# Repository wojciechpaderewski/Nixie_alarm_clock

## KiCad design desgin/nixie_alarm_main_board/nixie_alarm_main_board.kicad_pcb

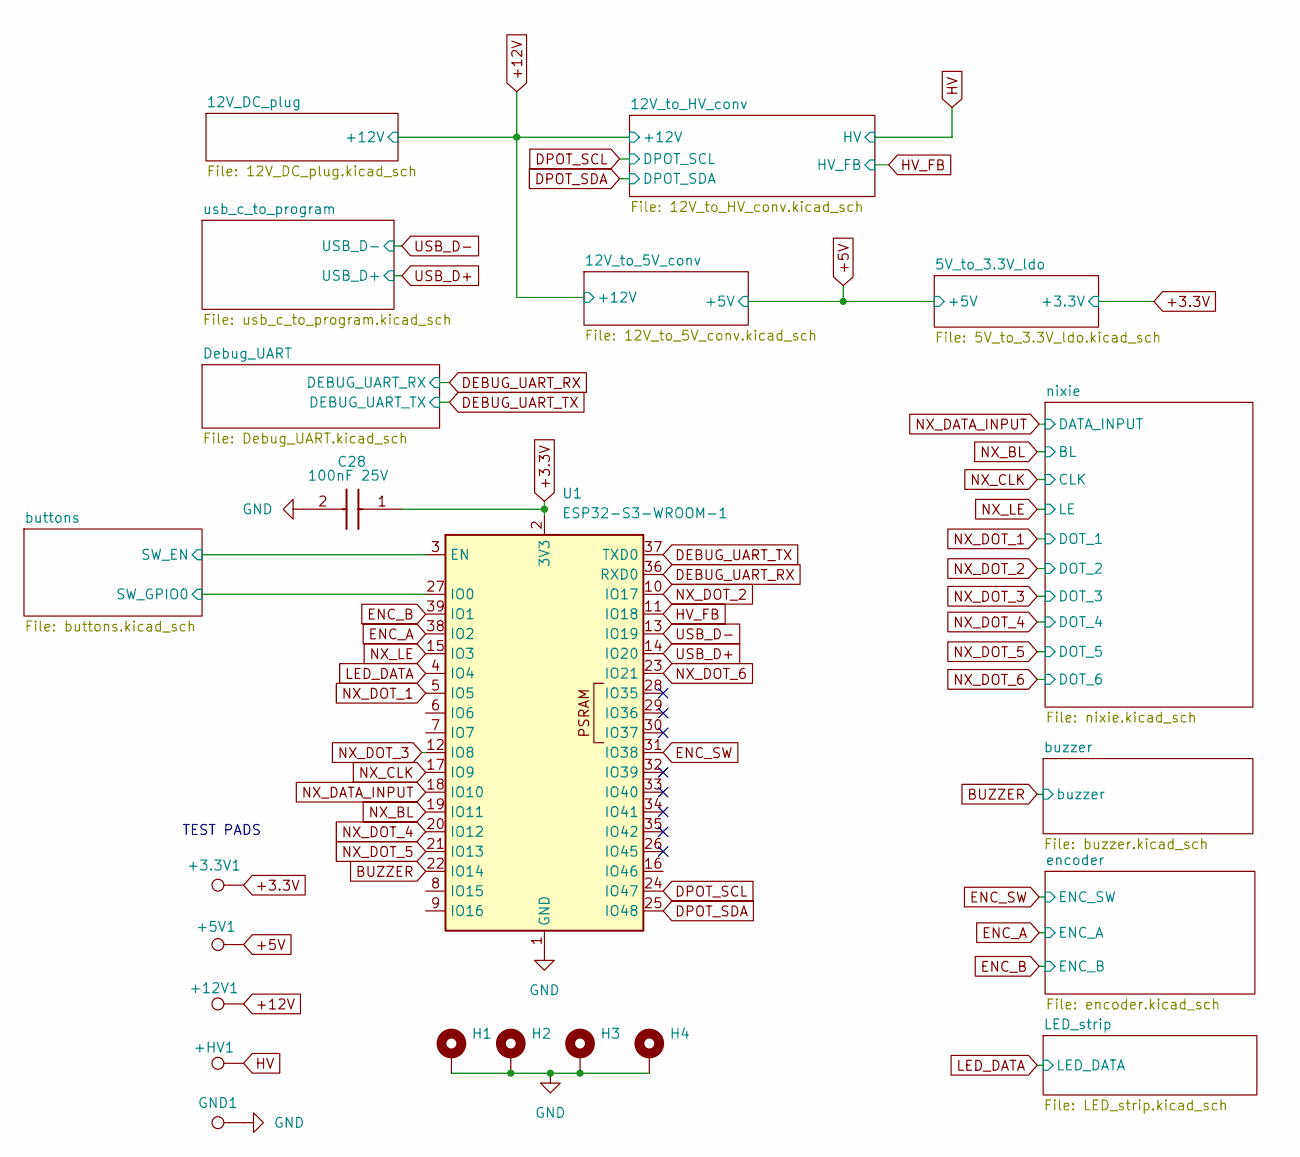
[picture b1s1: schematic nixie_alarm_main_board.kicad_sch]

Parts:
+3.3V1: +3.3V; TestPoint_Pad_D2.0mm
+5V1: +5V; TestPoint_Pad_D2.0mm
+12V1: +12V; TestPoint_Pad_D2.0mm
+HV1: +HV; TestPoint_Pad_D2.0mm
C28: 100nF 25V; C_0805_2012Metric_Pad1.18x1.45mm_HandSolder; Mouser Part Number 81-GRM033R71E101KA1J
GND1: GND; TestPoint_Pad_D2.0mm
H1, H2, H3, H4: MountingHole_Pad; MountingHole_3.2mm_M3_Pad_Via
U1: ESP32-S3-WROOM-1

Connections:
+3.3V: +3.3V1.1, C28.1, U1.2 (3V3); also elsewhere on the board
+5V: +5V1.1; also elsewhere on the board
+12V: +12V1.1; also elsewhere on the board
/buttons/SW_EN: U1.3 (EN); also elsewhere on the board
/buttons/SW_GPIO0: U1.27 (IO0); also elsewhere on the board
BUZZER: U1.22 (IO14); also elsewhere on the board
DEBUG_UART_RX: U1.36 (RXD0); also elsewhere on the board
DEBUG_UART_TX: U1.37 (TXD0); also elsewhere on the board
DPOT_SCL: U1.24 (IO47); also elsewhere on the board
DPOT_SDA: U1.25 (IO48); also elsewhere on the board
ENC_A: U1.38 (IO2); also elsewhere on the board
ENC_B: U1.39 (IO1); also elsewhere on the board
ENC_SW: U1.31 (IO38); also elsewhere on the board
GND: C28.2, GND1.1, H1.1, H2.1, H3.1, H4.1, U1.1 (GND), U1.40 (GND), U1.41 (GND); also elsewhere on the board
HV: +HV1.1; also elsewhere on the board
HV_FB: U1.11 (IO18); also elsewhere on the board
LED_DATA: U1.4 (IO4); also elsewhere on the board
NX_BL: U1.19 (IO11); also elsewhere on the board
NX_CLK: U1.17 (IO9); also elsewhere on the board
NX_DATA_INPUT: U1.18 (IO10); also elsewhere on the board
NX_DOT_1: U1.5 (IO5); also elsewhere on the board
NX_DOT_2: U1.10 (IO17); also elsewhere on the board
NX_DOT_3: U1.12 (IO8); also elsewhere on the board
NX_DOT_4: U1.20 (IO12); also elsewhere on the board
NX_DOT_5: U1.21 (IO13); also elsewhere on the board
NX_DOT_6: U1.23 (IO21); also elsewhere on the board
NX_LE: U1.15 (IO3); also elsewhere on the board
USB_D+: U1.14 (IO20); also elsewhere on the board
USB_D-: U1.13 (IO19); also elsewhere on the board

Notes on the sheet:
TEST PADS

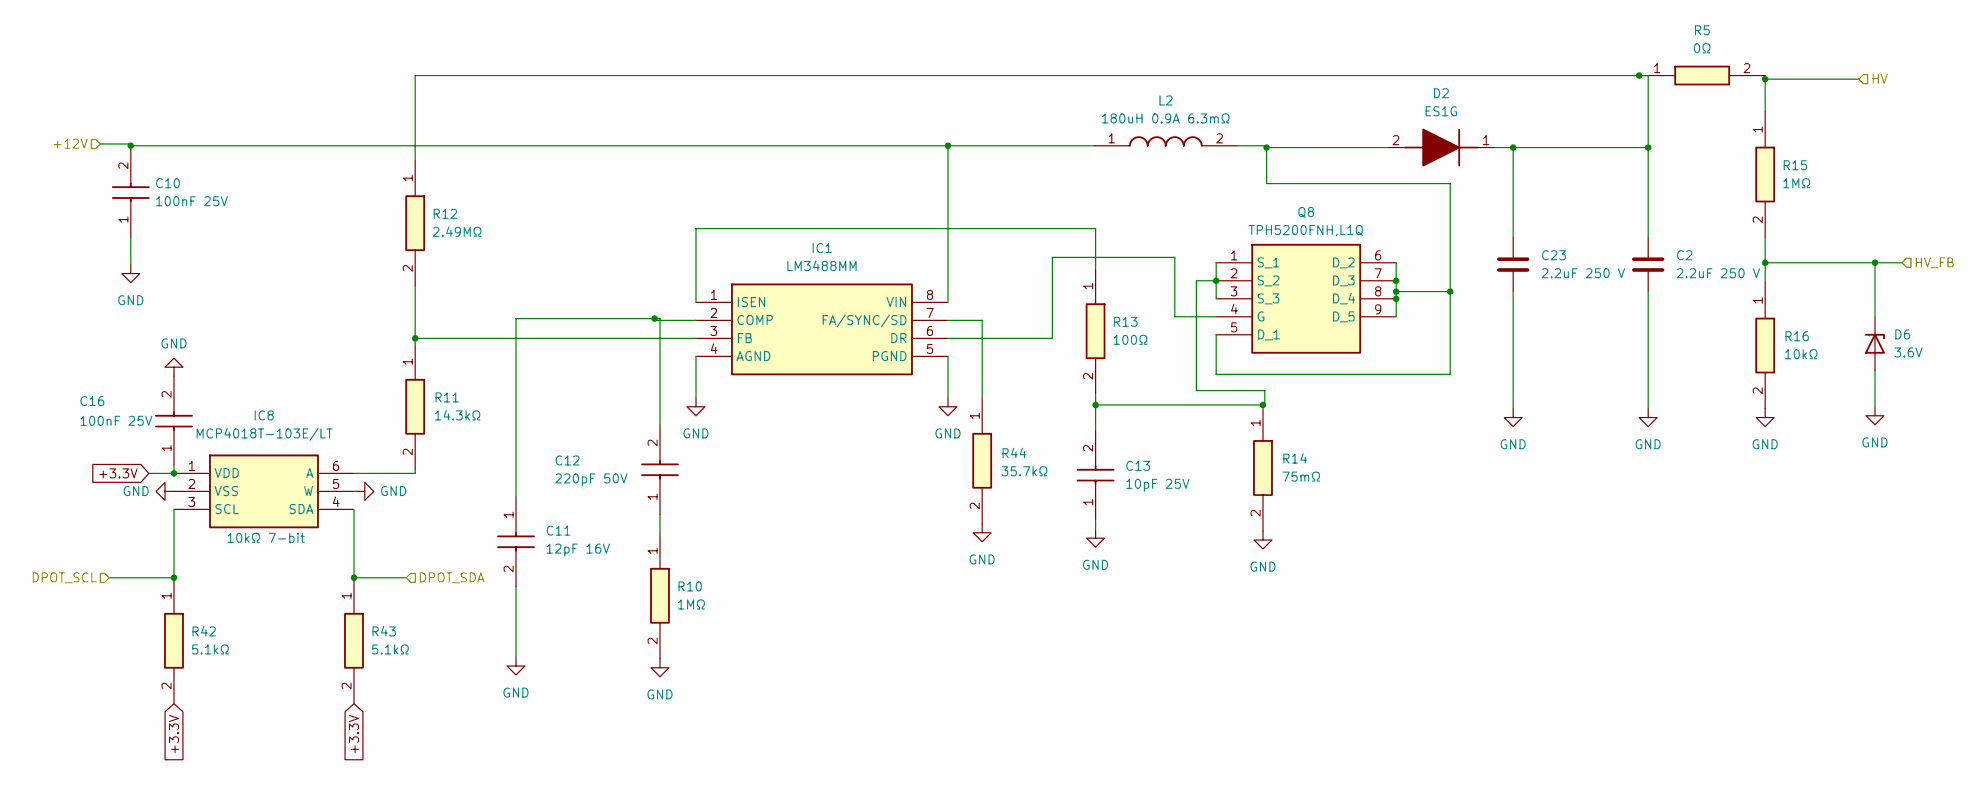
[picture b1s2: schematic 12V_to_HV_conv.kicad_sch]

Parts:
C2, C23: 2.2uF 250 V; C_2220_5750Metric_Pad1.97x5.40mm_HandSolder
C10, C16: 100nF 25V; C_0805_2012Metric_Pad1.18x1.45mm_HandSolder; Mouser Part Number 81-GRM033R71E101KA1J
C11: 12pF 16V; C0805; Mouser Part Number 80-C0805C332K5R
C12: 220pF 50V; C_0805_2012Metric_Pad1.18x1.45mm_HandSolder; Mouser Part Number 81-GRM033R71E101KA1J
C13: 10pF 25V; C_0805_2012Metric_Pad1.18x1.45mm_HandSolder; Mouser Part Number 81-GRM033R71E101KA1J
D2: ES1G; DIOM5227X260N; Mouser Part Number 512-ES1G
D6: 3.6V; D_0805_2012Metric_Pad1.15x1.40mm_HandSolder
IC1: LM3488MM; SOP65P490X110-8N; Mouser Part Number 926-LM3488MM
IC8: MCP4018T-103E/LT; SOT65P210X110-6N; Mouser Part Number 579-MCP4018T502ELT
L2: 180uH 0.9A 6.3mΩ; L_12x12mm_H6mm; Mouser Part Number 710-74437529203331
Q8: TPH5200FNH,L1Q; TPHR6503PL1LQ; Mouser Part Number 757-TPHR6503PL1LQ
R5: 0Ω; R_0805_2012Metric_Pad1.20x1.40mm_HandSolder; Mouser Part Number 71-CRCW0402-2.74K-E3
R10, R15: 1MΩ; R_1206_3216Metric_Pad1.30x1.75mm_HandSolder; Mouser Part Number 71-CRCW0402-2.74K-E3
R11: 14.3kΩ; R_0805_2012Metric_Pad1.20x1.40mm_HandSolder; Mouser Part Number 71-CRCW0402-2.74K-E3
R12: 2.49MΩ; R_1206_3216Metric_Pad1.30x1.75mm_HandSolder; Mouser Part Number 71-CRCW0402-2.74K-E3
R13: 100Ω; R_0805_2012Metric_Pad1.20x1.40mm_HandSolder; Mouser Part Number 71-CRCW0402-2.74K-E3
R14: 75mΩ; R_0805_2012Metric_Pad1.20x1.40mm_HandSolder; Mouser Part Number 667-ERJ-UP6D5101V
R16: 10kΩ; R_0805_2012Metric_Pad1.20x1.40mm_HandSolder; Mouser Part Number 71-CRCW0402-2.74K-E3
R42, R43: 5.1kΩ; R_0805_2012Metric_Pad1.20x1.40mm_HandSolder; Mouser Part Number 667-ERJ-UP6D5101V
R44: 35.7kΩ; R_0805_2012Metric_Pad1.20x1.40mm_HandSolder; Mouser Part Number 660-RK73H2ATTE1003F

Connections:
+3.3V: C16.1, IC8.1 (VDD), R42.2, R43.2; also elsewhere on the board
+12V: C10.2, IC1.8 (VIN), L2.1; also elsewhere on the board
DPOT_SCL: IC8.3 (SCL), R42.1; also elsewhere on the board
DPOT_SDA: IC8.4 (SDA), R43.1; also elsewhere on the board
GND: C2.2, C10.1, C11.2, C13.1, C16.2, C23.2, D6.2 (A), IC1.4 (AGND), IC1.5 (PGND), IC8.2 (VSS), IC8.5 (W), R10.2, R14.2, R16.2, R44.2; also elsewhere on the board
HV: R5.2, R15.1; also elsewhere on the board
HV_FB: D6.1 (K), R15.2, R16.1; also elsewhere on the board
unnamed: C12.1, R10.1
unnamed: D2.2 (A), L2.2, Q8.5 (D_1), Q8.6 (D_2), Q8.7 (D_3), Q8.8 (D_4), Q8.9 (D_5)
unnamed: C2.1, C23.1, D2.1 (K), R5.1, R12.1
unnamed: C11.1, C12.2, IC1.2 (COMP)
unnamed: IC1.6 (DR), Q8.4 (G)
unnamed: IC1.7 (FA/SYNC/SD), R44.1
unnamed: IC1.3 (FB), R11.1, R12.2
unnamed: IC1.1 (ISEN), R13.1
unnamed: IC8.6 (A), R11.2
unnamed: C13.2, Q8.1 (S_1), Q8.2 (S_2), Q8.3 (S_3), R13.2, R14.1

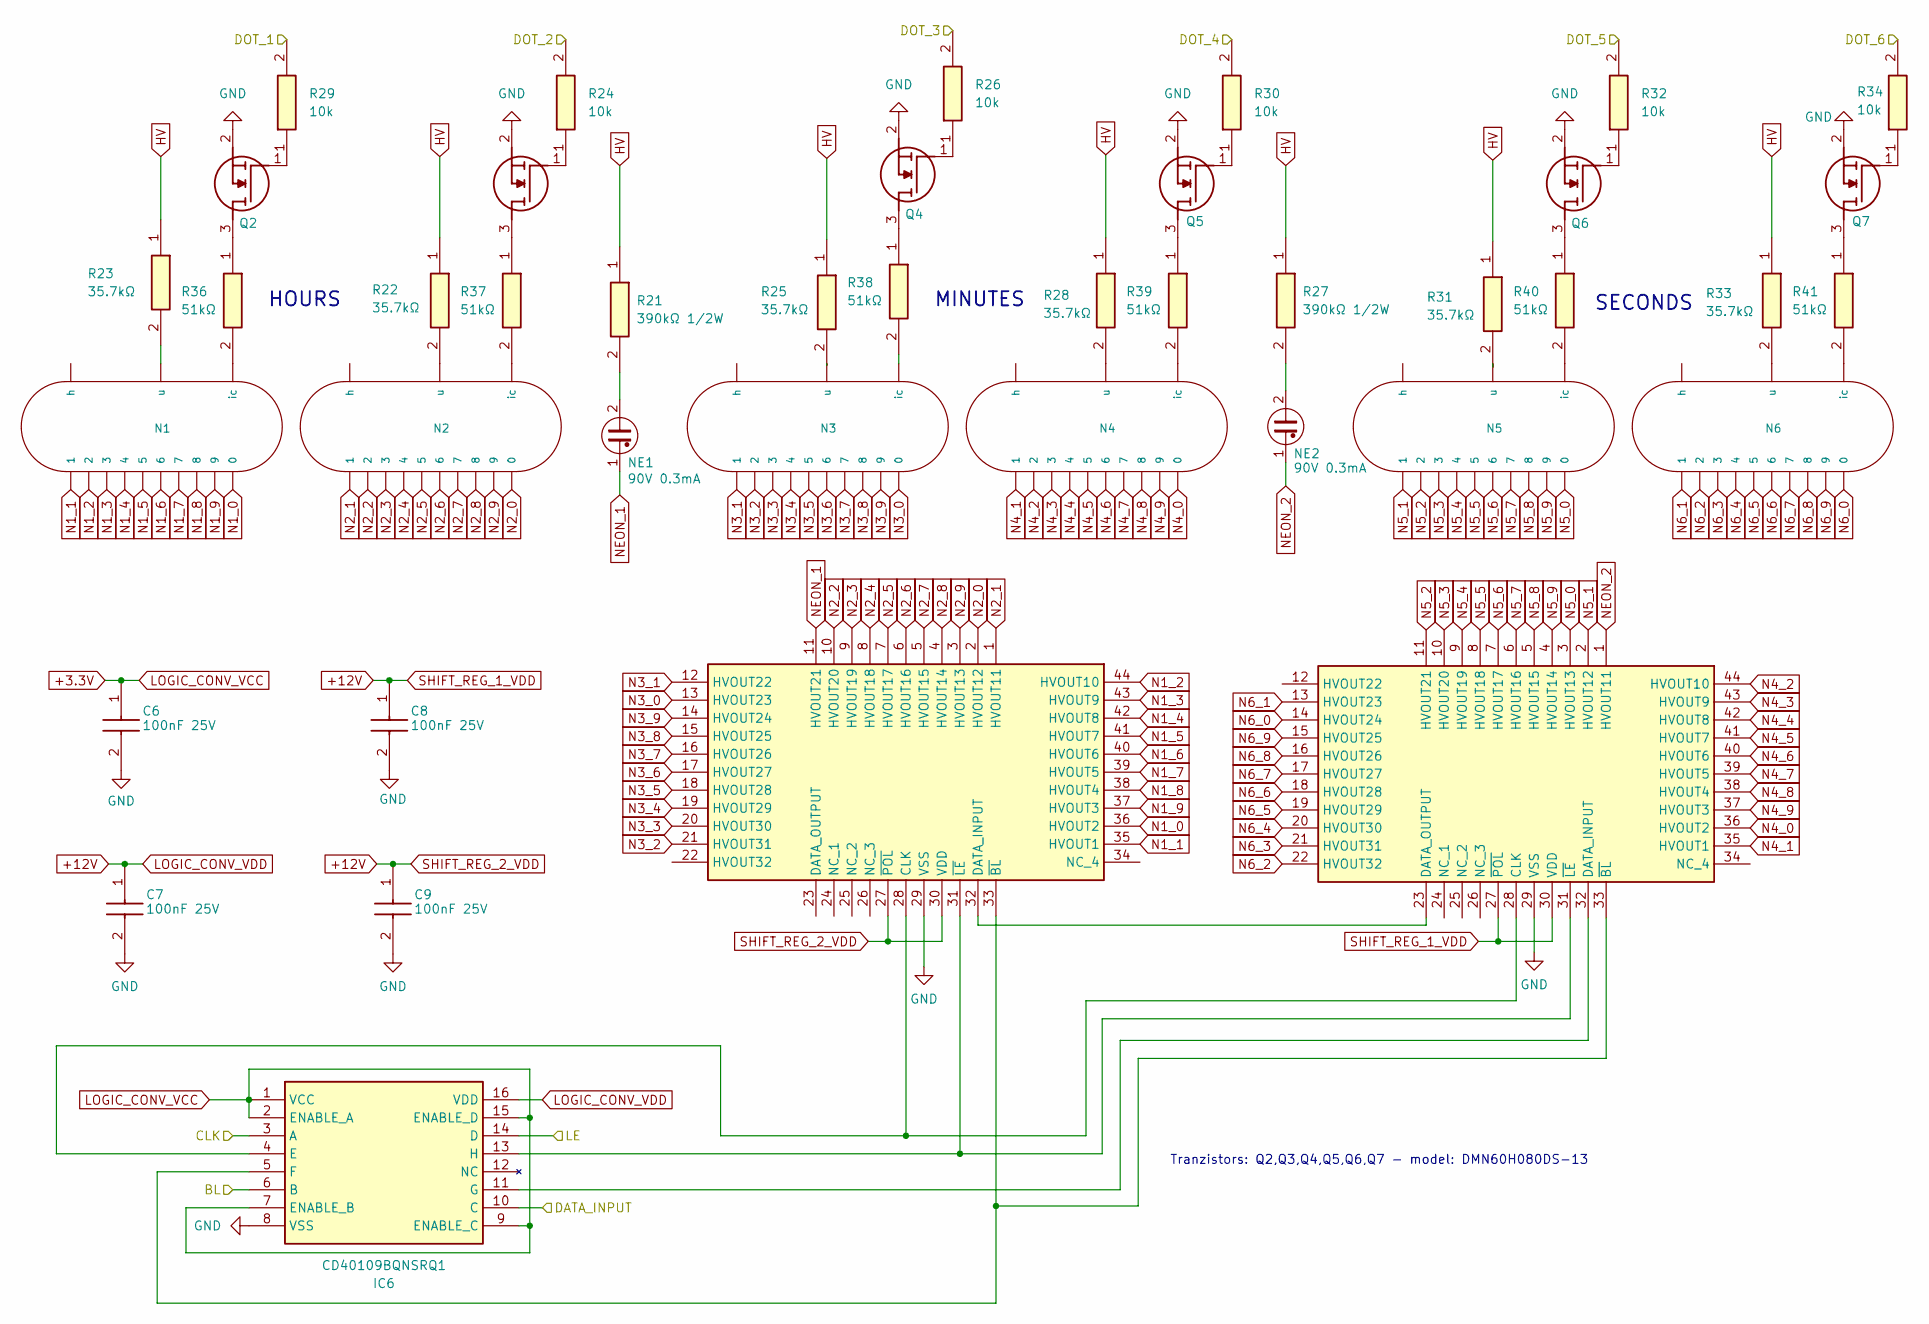
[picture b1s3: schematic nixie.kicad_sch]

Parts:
C6, C7, C8, C9: 100nF 25V; C_0805_2012Metric_Pad1.18x1.45mm_HandSolder; Mouser Part Number 81-GRM033R71E101KA1J
IC2, IC4: HV5530PG-G; QFP80P1390X1390X235-44N; Mouser Part Number 689-HV5530PG-G
IC6: CD40109BQNSRQ1; SOIC127P780X200-16N; Mouser Part Number 595-CD40109BQNSRQ1
N1, N2, N3, N4, N5, N6: Z570M
NE1, NE2: 90V 0.3mA; neon_lamp
Q2, Q3, Q4, Q5, Q6, Q7: DMN60H080DS-13; SOT96P240X110-3N; Mouser Part Number 621-DMN60H080DS-13
R21, R27: 390kΩ 1/2W; R_0805_2012Metric_Pad1.20x1.40mm_HandSolder; Mouser Part Number 660-RK73H2ATTE1003F
R22, R23, R25, R28, R31, R33: 35.7kΩ; R_0805_2012Metric_Pad1.20x1.40mm_HandSolder; Mouser Part Number 660-RK73H2ATTE1003F
R24, R26, R29, R30, R32, R34: 10k; R_0805_2012Metric_Pad1.20x1.40mm_HandSolder; Mouser Part Number 667-ERJ-UP6D5101V
R36, R37, R38, R39, R40, R41: 51kΩ; R_0805_2012Metric_Pad1.20x1.40mm_HandSolder; Mouser Part Number 660-RK73H2ATTE1003F

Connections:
+3.3V: C6.1, IC6.1 (VCC), IC6.2 (ENABLE_A), IC6.7 (ENABLE_B), IC6.9 (ENABLE_C), IC6.15 (ENABLE_D); also elsewhere on the board
+12V: C7.1, C8.1, C9.1, IC2.27 (~POL), IC2.30 (VDD), IC4.27 (~POL), IC4.30 (VDD), IC6.16 (VDD); also elsewhere on the board
GND: C6.2, C7.2, C8.2, C9.2, IC2.29 (VSS), IC4.29 (VSS), IC6.8 (VSS), Q2.2 (S), Q3.2 (S), Q4.2 (S), Q5.2 (S), Q6.2 (S), Q7.2 (S); also elsewhere on the board
HV: R21.1, R22.1, R23.1, R25.1, R27.1, R28.1, R31.1, R33.1; also elsewhere on the board
N1_0: IC2.36 (HVOUT2), N1.0
N1_1: IC2.35 (HVOUT1), N1.1
N1_2: IC2.44 (HVOUT10), N1.2
N1_3: IC2.43 (HVOUT9), N1.3
N1_4: IC2.42 (HVOUT8), N1.4
N1_5: IC2.41 (HVOUT7), N1.5
N1_6: IC2.40 (HVOUT6), N1.6
N1_7: IC2.39 (HVOUT5), N1.7
N1_8: IC2.38 (HVOUT4), N1.8
N1_9: IC2.37 (HVOUT3), N1.9
N2_0: IC2.2 (HVOUT12), N2.0
N2_1: IC2.1 (HVOUT11), N2.1
N2_2: IC2.10 (HVOUT20), N2.2
N2_3: IC2.9 (HVOUT19), N2.3
N2_4: IC2.8 (HVOUT18), N2.4
N2_5: IC2.7 (HVOUT17), N2.5
N2_6: IC2.6 (HVOUT16), N2.6
N2_7: IC2.5 (HVOUT15), N2.7
N2_8: IC2.4 (HVOUT14), N2.8
N2_9: IC2.3 (HVOUT13), N2.9
N3_0: IC2.13 (HVOUT23), N3.0
N3_1: IC2.12 (HVOUT22), N3.1
N3_2: IC2.21 (HVOUT31), N3.2
N3_3: IC2.20 (HVOUT30), N3.3
N3_4: IC2.19 (HVOUT29), N3.4
N3_5: IC2.18 (HVOUT28), N3.5
N3_6: IC2.17 (HVOUT27), N3.6
N3_7: IC2.16 (HVOUT26), N3.7
N3_8: IC2.15 (HVOUT25), N3.8
N3_9: IC2.14 (HVOUT24), N3.9
N4_0: IC4.36 (HVOUT2), N4.0
N4_1: IC4.35 (HVOUT1), N4.1
N4_2: IC4.44 (HVOUT10), N4.2
N4_3: IC4.43 (HVOUT9), N4.3
N4_4: IC4.42 (HVOUT8), N4.4
N4_5: IC4.41 (HVOUT7), N4.5
N4_6: IC4.40 (HVOUT6), N4.6
N4_7: IC4.39 (HVOUT5), N4.7
N4_8: IC4.38 (HVOUT4), N4.8
N4_9: IC4.37 (HVOUT3), N4.9
N5_0: IC4.3 (HVOUT13), N5.0
N5_1: IC4.2 (HVOUT12), N5.1
N5_2: IC4.11 (HVOUT21), N5.2
N5_3: IC4.10 (HVOUT20), N5.3
N5_4: IC4.9 (HVOUT19), N5.4
N5_5: IC4.8 (HVOUT18), N5.5
N5_6: IC4.7 (HVOUT17), N5.6
N5_7: IC4.6 (HVOUT16), N5.7
N5_8: IC4.5 (HVOUT15), N5.8
N5_9: IC4.4 (HVOUT14), N5.9
N6_0: IC4.14 (HVOUT24), N6.0
N6_1: IC4.13 (HVOUT23), N6.1
N6_2: IC4.22 (HVOUT32), N6.2
N6_3: IC4.21 (HVOUT31), N6.3
N6_4: IC4.20 (HVOUT30), N6.4
N6_5: IC4.19 (HVOUT29), N6.5
N6_6: IC4.18 (HVOUT28), N6.6
N6_7: IC4.17 (HVOUT27), N6.7
N6_8: IC4.16 (HVOUT26), N6.8
N6_9: IC4.15 (HVOUT25), N6.9
NEON_1: IC2.11 (HVOUT21), NE1.1
NEON_2: IC4.1 (HVOUT11), NE2.1
NX_BL: IC6.6 (B); also elsewhere on the board
NX_CLK: IC6.3 (A); also elsewhere on the board
NX_DATA_INPUT: IC6.10 (C); also elsewhere on the board
NX_DOT_1: R29.2; also elsewhere on the board
NX_DOT_2: R24.2; also elsewhere on the board
NX_DOT_3: R26.2; also elsewhere on the board
NX_DOT_4: R30.2; also elsewhere on the board
NX_DOT_5: R32.2; also elsewhere on the board
NX_DOT_6: R34.2; also elsewhere on the board
NX_LE: IC6.14 (D); also elsewhere on the board
unnamed: IC2.28 (CLK), IC4.28 (CLK), IC6.4 (E)
unnamed: IC2.32 (DATA_INPUT), IC4.23 (DATA_OUTPUT)
unnamed: IC2.33 (~BL), IC4.33 (~BL), IC6.5 (F)
unnamed: IC2.31 (~LE), IC4.31 (~LE), IC6.13 (H)
unnamed: IC4.32 (DATA_INPUT), IC6.11 (G)
unnamed: N1.ic, R36.2
unnamed: N1.u, R23.2
unnamed: N2.ic, R37.2
unnamed: N2.u, R22.2
unnamed: N3.ic, R38.2
unnamed: N3.u, R25.2
unnamed: N4.ic, R39.2
unnamed: N4.u, R28.2
unnamed: N5.ic, R40.2
unnamed: N5.u, R31.2
unnamed: N6.ic, R41.2
unnamed: N6.u, R33.2
unnamed: NE1.2, R21.2
unnamed: NE2.2, R27.2
unnamed: Q2.3 (D), R36.1
unnamed: Q2.1 (G), R29.1
unnamed: Q3.3 (D), R37.1
unnamed: Q3.1 (G), R24.1
unnamed: Q4.3 (D), R38.1
unnamed: Q4.1 (G), R26.1
unnamed: Q5.3 (D), R39.1
unnamed: Q5.1 (G), R30.1
unnamed: Q6.3 (D), R40.1
unnamed: Q6.1 (G), R32.1
unnamed: Q7.3 (D), R41.1
unnamed: Q7.1 (G), R34.1

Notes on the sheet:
HOURS
Tranzistors: Q2,Q3,Q4,Q5,Q6,Q7 - model: DMN60H080DS-13
SECONDS
MINUTES

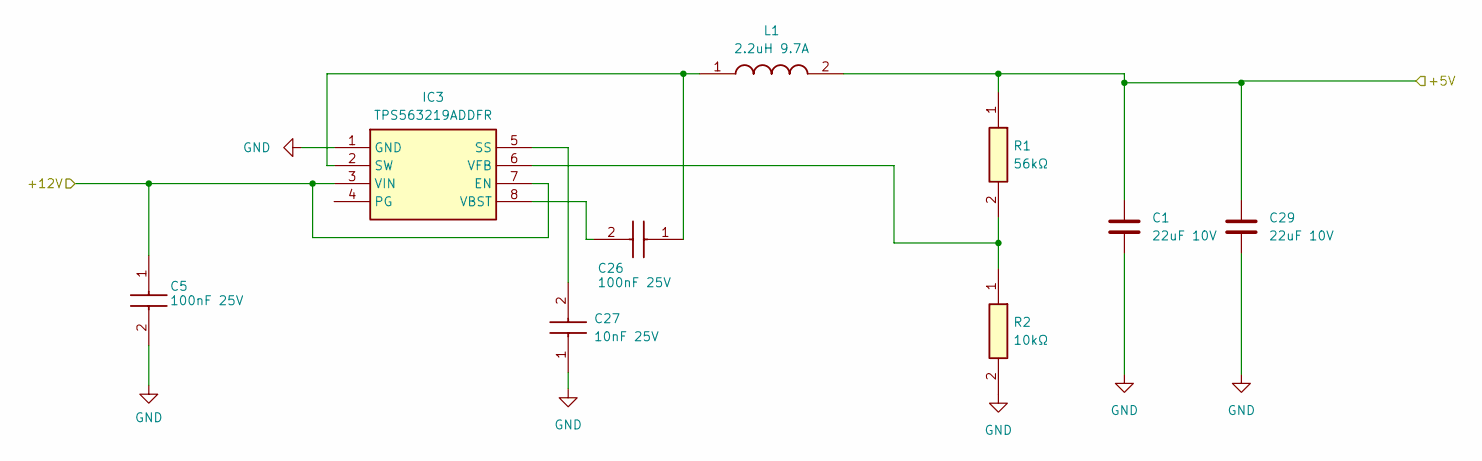
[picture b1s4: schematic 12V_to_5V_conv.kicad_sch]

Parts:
C1, C29: 22uF 10V; C_0805_2012Metric_Pad1.18x1.45mm_HandSolder
C5, C26: 100nF 25V; C_0805_2012Metric_Pad1.18x1.45mm_HandSolder; Mouser Part Number 81-GRM033R71E101KA1J
C27: 10nF 25V; C_0805_2012Metric_Pad1.18x1.45mm_HandSolder; Mouser Part Number 81-GRM033R71E101KA1J
IC3: TPS563219ADDFR; SOT65P280X110-8N; Mouser Part Number 595-TPS563219ADDFR
L1: 2.2uH 9.7A; SRP5030CA4R7M; Mouser Part Number 652-SRP5030CA-2R2M
R1: 56kΩ; R_0805_2012Metric_Pad1.20x1.40mm_HandSolder; Mouser Part Number 667-ERJ-UP6D5101V
R2: 10kΩ; R_0805_2012Metric_Pad1.20x1.40mm_HandSolder; Mouser Part Number 667-ERJ-UP6D5101V

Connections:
+5V: C1.1, C29.1, L1.2, R1.1; also elsewhere on the board
+12V: C5.1, IC3.3 (VIN), IC3.7 (EN); also elsewhere on the board
GND: C1.2, C5.2, C27.1, C29.2, IC3.1 (GND), R2.2; also elsewhere on the board
unnamed: C27.2, IC3.5 (SS)
unnamed: C26.1, IC3.2 (SW), L1.1
unnamed: C26.2, IC3.8 (VBST)
unnamed: IC3.6 (VFB), R1.2, R2.1

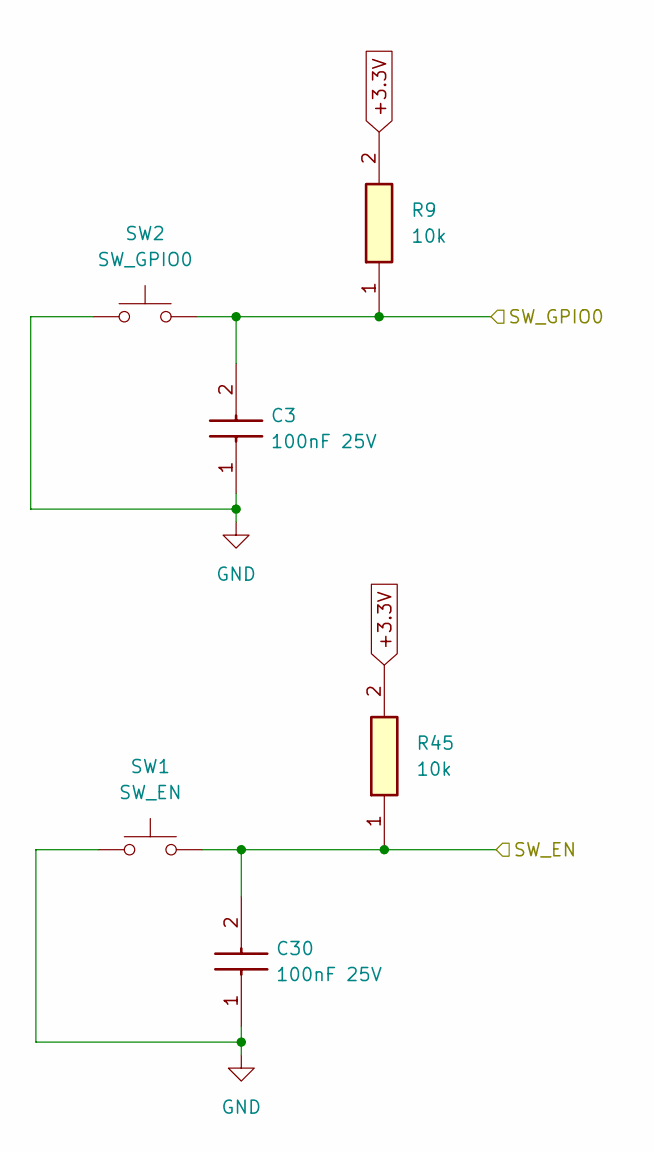
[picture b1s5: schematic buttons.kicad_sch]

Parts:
C3, C30: 100nF 25V; C_0805_2012Metric_Pad1.18x1.45mm_HandSolder; Mouser Part Number 81-GRM033R71E101KA1J
R9, R45: 10k; R_0805_2012Metric_Pad1.20x1.40mm_HandSolder; Mouser Part Number 667-ERJ-UP6D5101V
SW1: SW_EN; B3U1000PM
SW2: SW_GPIO0; B3U1000PM

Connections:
+3.3V: R9.2, R45.2; also elsewhere on the board
/buttons/SW_EN: C30.2, R45.1, SW1.2; also elsewhere on the board
/buttons/SW_GPIO0: C3.2, R9.1, SW2.2; also elsewhere on the board
GND: C3.1, C30.1, SW1.1, SW2.1; also elsewhere on the board

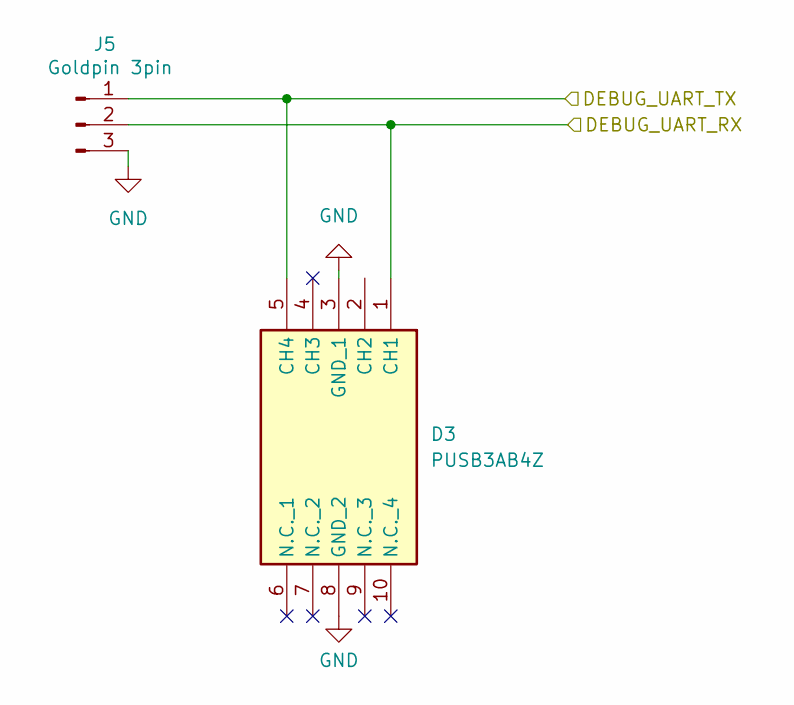
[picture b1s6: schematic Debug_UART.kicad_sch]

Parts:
D3: PUSB3AB4Z; SON50P100X250X50-10N; Mouser Part Number 771-PUSB3AB4Z
J5: Goldpin 3pin; PinHeader_1x03_P2.54mm_Horizontal

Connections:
DEBUG_UART_RX: D3.1 (CH1), J5.2; also elsewhere on the board
DEBUG_UART_TX: D3.5 (CH4), J5.1; also elsewhere on the board
GND: D3.3 (GND_1), D3.8 (GND_2), J5.3; also elsewhere on the board

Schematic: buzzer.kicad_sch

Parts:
D5: CDBUR0520; D_0603_1608Metric_Pad1.05x0.95mm_HandSolder
LS1: CEM-1203_42_; Mouser Part Number 490-CEM-1203(42)
Q1: DMN60H080DS-13; SOT96P240X110-3N; Mouser Part Number 621-DMN60H080DS-13
R35: 10k; R_0805_2012Metric_Pad1.20x1.40mm_HandSolder; Mouser Part Number 667-ERJ-UP6D5101V

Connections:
+3.3V: D5.1 (K), LS1.1 (+); also elsewhere on the board
BUZZER: R35.2; also elsewhere on the board
GND: Q1.2 (S); also elsewhere on the board
unnamed: D5.2 (A), LS1.2 (-), Q1.3 (D)
unnamed: Q1.1 (G), R35.1

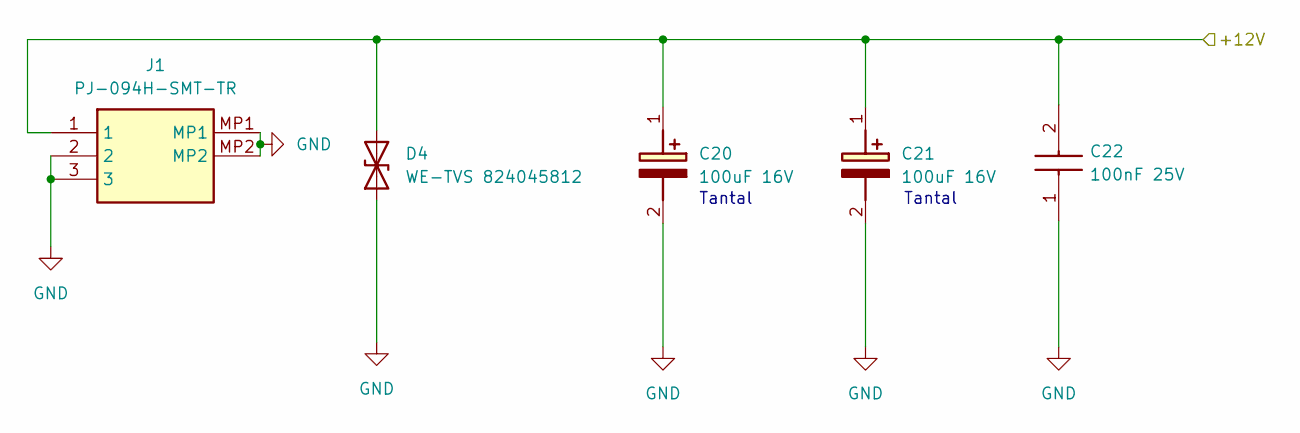
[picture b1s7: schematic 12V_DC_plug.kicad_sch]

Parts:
C20, C21: 100uF 16V; CAPPM7344X310N; Mouser Part Number 581-TAJD107K016R
C22: 100nF 25V; C_0805_2012Metric_Pad1.18x1.45mm_HandSolder; Mouser Part Number 81-GRM033R71E101KA1J
D4: WE-TVS 824045812; DFN-1610-2
J1: PJ-094H-SMT-TR; PJ094HSMTTR; Mouser Part Number 490-PJ-094H-SMT-TR

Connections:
+12V: C20.1 (+), C21.1 (+), C22.2, D4.2 (A2), J1.1; also elsewhere on the board
GND: C20.2 (-), C21.2 (-), C22.1, D4.1 (A1), J1.2, J1.3, J1.MP1, J1.MP2; also elsewhere on the board

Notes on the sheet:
Tantal
Tantal

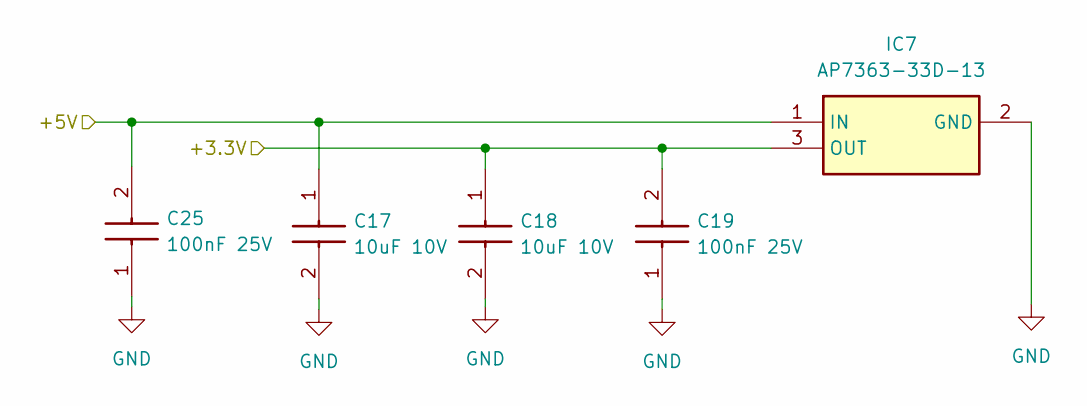
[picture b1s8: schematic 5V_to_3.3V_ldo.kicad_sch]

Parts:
C17, C18: 10uF 10V; C_0805_2012Metric_Pad1.18x1.45mm_HandSolder; Mouser Part Number 187-CL21A106KPFNNNE
C19, C25: 100nF 25V; C_0805_2012Metric_Pad1.18x1.45mm_HandSolder; Mouser Part Number 81-GRM033R71E101KA1J
IC7: AP7363-33D-13; AP736333D13; Mouser Part Number 621-AP7363-33D-13

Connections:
+3.3V: C18.1, C19.2, IC7.3 (OUT); also elsewhere on the board
+5V: C17.1, C25.2, IC7.1 (IN); also elsewhere on the board
GND: C17.2, C18.2, C19.1, C25.1, IC7.2 (GND); also elsewhere on the board

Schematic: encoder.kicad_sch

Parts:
C4, C14, C15: 100nF 25V; C_0805_2012Metric_Pad1.18x1.45mm_HandSolder; Mouser Part Number 81-GRM033R71E101KA1J
ENC1: RotaryEncoder_Switch; PEC12R41BBFS0012
R7, R8, R17, R18, R19, R20: 10k; R_0805_2012Metric_Pad1.20x1.40mm_HandSolder; Mouser Part Number 667-ERJ-UP6D5101V

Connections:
+5V: R7.2, R17.2, R18.1; also elsewhere on the board
ENC_A: C15.1, R20.2; also elsewhere on the board
ENC_B: C14.1, R19.2; also elsewhere on the board
ENC_SW: C4.1, R8.2; also elsewhere on the board
GND: C4.2, C14.2, C15.2, ENC1.2, ENC1.C1, ENC1.MH1, ENC1.MH2 (MH12); also elsewhere on the board
unnamed: ENC1.1, R7.1, R8.1
unnamed: ENC1.A1, R17.1, R20.1
unnamed: ENC1.B1, R18.2, R19.1

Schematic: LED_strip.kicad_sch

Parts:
C24: 100nF 25V; C_0805_2012Metric_Pad1.18x1.45mm_HandSolder; Mouser Part Number 81-GRM033R71E101KA1J
J2: JST XH 2.54 3 pin; JST_XH_S3B-XH-A-1_1x03_P2.50mm_Horizontal
R6: 100Ω; R_0805_2012Metric_Pad1.20x1.40mm_HandSolder; Mouser Part Number 667-ERJ-UP6D5101V

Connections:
+5V: C24.1, J2.1; also elsewhere on the board
GND: C24.2, J2.3; also elsewhere on the board
LED_DATA: R6.2; also elsewhere on the board
unnamed: J2.2, R6.1

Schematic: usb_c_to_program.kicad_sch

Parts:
D1: PUSB3AB4Z; SON50P100X250X50-10N; Mouser Part Number 771-PUSB3AB4Z
J3: USB_C_Receptacle_USB2.0_16P; USB_C_Receptacle_GCT_USB4105-xx-A_16P_TopMnt_Horizontal
R3, R4: 5.1kΩ; R_0805_2012Metric_Pad1.20x1.40mm_HandSolder; Mouser Part Number 667-ERJ-UP6D5101V

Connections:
GND: D1.3 (GND_1), D1.8 (GND_2), J3.A1 (GND), J3.A12 (GND), J3.B1 (GND), J3.B12 (GND), J3.S1 (SHIELD), R3.2, R4.2; also elsewhere on the board
unnamed: J3.A5 (CC1), R4.1
unnamed: J3.B5 (CC2), R3.1
USB_D+: D1.4 (CH3), D1.5 (CH4), J3.A6 (D+), J3.B6 (D+); also elsewhere on the board
USB_D-: D1.1 (CH1), D1.2 (CH2), J3.A7 (D-), J3.B7 (D-); also elsewhere on the board

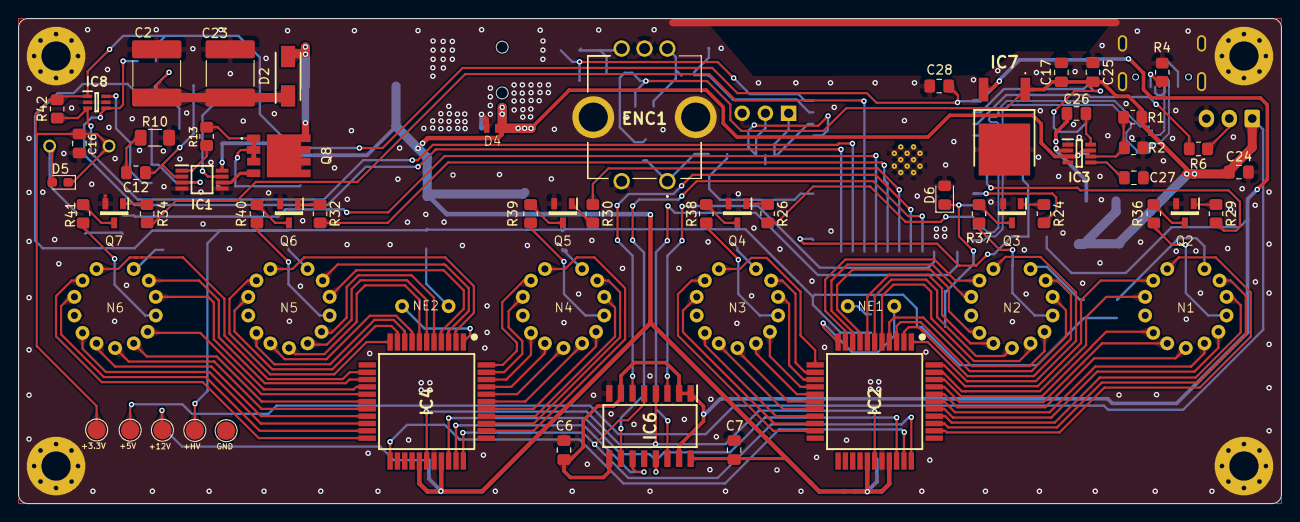
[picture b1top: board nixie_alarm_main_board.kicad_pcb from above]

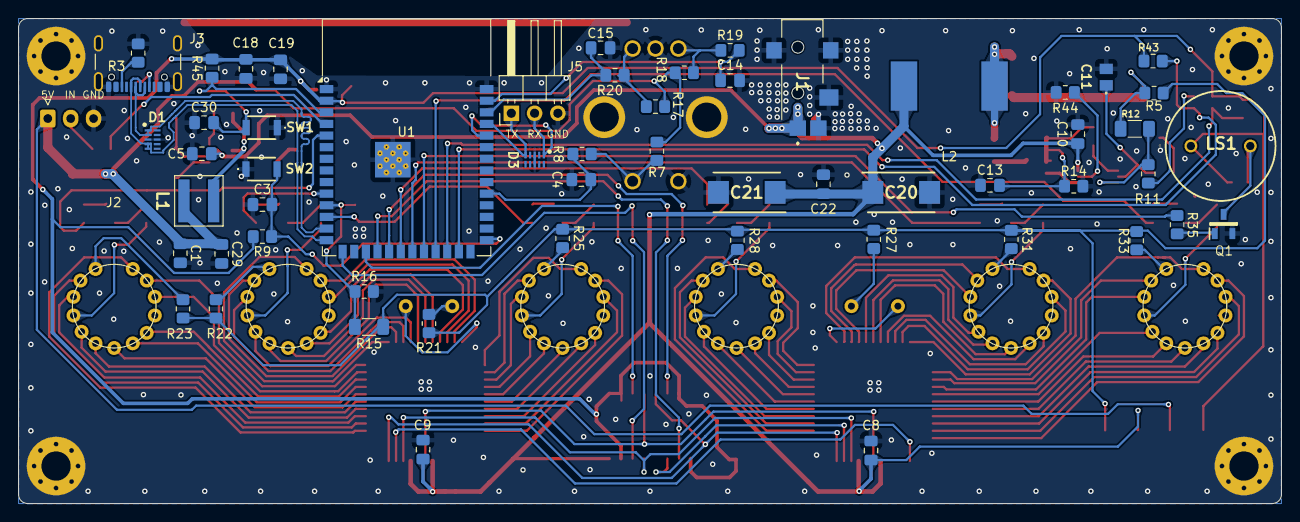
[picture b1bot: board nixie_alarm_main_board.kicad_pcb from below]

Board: 2 copper layers, 138.0 x 53.0 mm, 124 parts (57 on the bottom side), 144 nets.

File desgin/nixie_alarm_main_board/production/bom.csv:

Designator,Footprint,Quantity,Value,LCSC Part #
+12V1,TestPoint_Pad_D2.0mm,1,+12V,
+3.3V1,TestPoint_Pad_D2.0mm,1,+3.3V,
+5V1,TestPoint_Pad_D2.0mm,1,+5V,
+HV1,TestPoint_Pad_D2.0mm,1,+HV,
"C1, C29",0805,2,22uF 10V,
"C10, C14, C15, C16, C19, C22, C24, C25, C26, C28, C3, C30, C4, C5, C6, C7, C8, C9",0805,18,100nF 25V,
C11,C0805,1,12pF 16V,
C12,0805,1,220pF 50V,
C13,0805,1,10pF 25V,
"C17, C18",0805,2,10uF 10V,
"C2, C23",2220,2,2.2uF 250 V,
"C20, C21",CAPPM7344X310N,2,100uF 16V,
C27,0805,1,10nF 25V,
"D1, D3",SON50P100X250X50-10N,2,PUSB3AB4Z,
D2,DIOM5227X260N,1,ES1G,
D4,DFN-1610-2,1,WE-TVS 824045812,
D5,0603,1,CDBUR0520,
D6,0805,1,3.6V,
ENC1,PEC12R41BBFS0012,1,RotaryEncoder_Switch,
GND1,TestPoint_Pad_D2.0mm,1,GND,
IC1,SOP65P490X110-8N,1,LM3488MM,
"IC2, IC4",QFP80P1390X1390X235-44N,2,HV5530PG-G,
IC3,SOT65P280X110-8N,1,TPS563219ADDFR,
IC6,SOIC127P780X200-16N,1,CD40109BQNSRQ1,
IC7,AP736333D13,1,AP7363-33D-13,
IC8,SOT65P210X110-6N,1,MCP4018T-103E/LT,
J1,PJ094HSMTTR,1,PJ-094H-SMT-TR,
J2,JST_XH_S3B-XH-A-1_1x03_P2.50mm_Horizontal,1,JST XH 2.54 3 pin,
J3,USB_C_Receptacle_GCT_USB4105-xx-A_16P_TopMnt_Horizontal,1,USB_C_Receptacle_USB2.0_16P,
J5,PinHeader_1x03_P2.54mm_Horizontal,1,Goldpin 3pin,
L1,SRP5030CA4R7M,1,2.2uH 9.7A,
L2,L_12x12mm_H6mm,1,180uH 0.9A 6.3mΩ,
LS1,CEM-1203_42_,1,CEM-1203_42_,
"N1, N2, N3, N4, N5, N6",Z570M,6,Z570M,
"NE1, NE2",neon_lamp,2,90V 0.3mA,
"Q1, Q2, Q3, Q4, Q5, Q6, Q7",SOT96P240X110-3N,7,DMN60H080DS-13,
Q8,TPHR6503PL1LQ,1,"TPH5200FNH,L1Q",
R1,0805,1,56kΩ,
"R10, R15",1206,2,1MΩ,
R11,0805,1,14.3kΩ,
R12,1206,1,2.49MΩ,
"R13, R6",0805,2,100Ω,
R14,0805,1,75mΩ,
"R16, R2",0805,2,10kΩ,
"R17, R18, R19, R20, R24, R26, R29, R30, R32, R34, R35, R45, R7, R8, R9",0805,15,10k,
"R21, R27",0805,2,390kΩ 1/2W,
"R22, R23, R25, R28, R31, R33, R44",0805,7,35.7kΩ,
"R3, R4, R42, R43",0805,4,5.1kΩ,
"R36, R37, R38, R39, R40, R41",0805,6,51kΩ,
R5,0805,1,0Ω,
SW1,B3U1000PM,1,SW_EN,
SW2,B3U1000PM,1,SW_GPIO0,
U1,ESP32-S3-WROOM-1,1,ESP32-S3-WROOM-1,

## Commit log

2024-02-24 nixie tube params
2024-06-14 raport part 1
2024-08-13 schematic v1
2024-09-02 filter caps
2024-09-03 new rezistors
2024-09-03 new caps footprint
2024-09-03 new hv conv desgin
2024-09-04 traces for nixie tubes
2024-09-07 all components in board footprint
2024-09-08 board v1
2024-09-09 ground
2024-09-10 new layout
2024-09-11 hv section
2024-09-12 new board v1
2024-09-14 elements sings fixed
2024-09-15 add more detalis
2024-09-17 copper border
2024-09-18 little fixes
2024-09-19 label fix
2024-10-06 tvs protection try
2024-10-07 tvs added
2024-10-09 fixes added
2024-10-09 final fixes
2024-10-09 little adujstments
2024-10-10 usb c module describe
2024-10-14 new border
2024-10-14 dc plug module describe
2024-10-15 conv-table
2024-10-16 new conv capacitors
2024-10-16 border fix and drc check
2024-10-16 koncepcja układu
2024-10-17 rejestry
2024-10-20 new latex structure
2024-10-21 zener diode on fb
2024-10-23 fixed latex issue
2024-10-23 hv part1
2024-10-24 hv conv i schemat blokowy
2024-11-03 board v2
2024-11-03 after marge
2024-11-11 added buttons
2024-11-12 label fixes
2024-11-13 new gerbers
2024-11-13 gerbers
2024-11-14 toolkit
2024-11-14 marged with board v2
2024-11-14 nixie teoria
2024-11-17 serwery czasu
2024-11-17 refactor part 1
2024-11-18 refactor part 2
2024-11-18 encoder i buzzer
2024-11-20 refactor part 3
2024-11-20 fixes
2024-11-27 rejestry i ledy
2024-11-27 PCB added
2024-11-27 review
2024-12-02 more fixes
2024-12-06 montaz
2024-12-06 program
2024-12-06 pomiary
2024-12-07 testy
2024-12-07 podsumowanie
2024-12-08 nearly end
2024-12-12 fixing bad words
2024-12-12 checking part 1
2024-12-12 checking part 2
2024-12-15 finale
2024-12-15 finale 2 xd
